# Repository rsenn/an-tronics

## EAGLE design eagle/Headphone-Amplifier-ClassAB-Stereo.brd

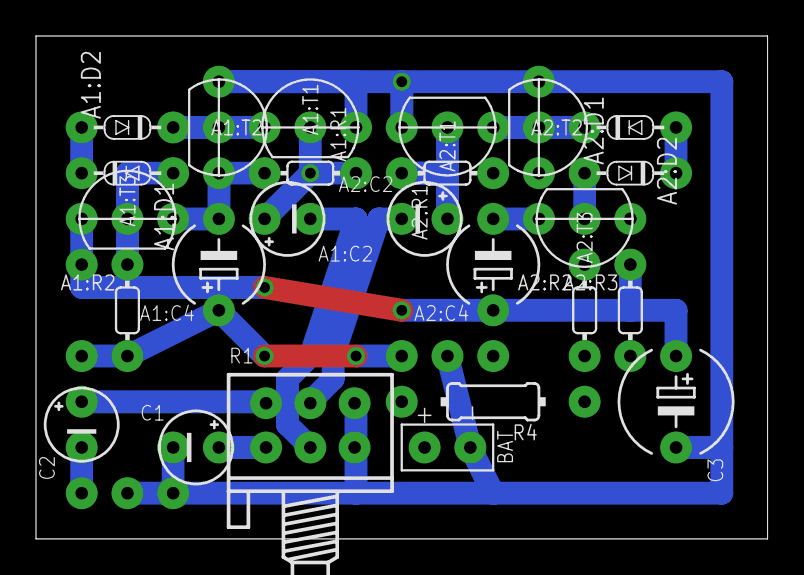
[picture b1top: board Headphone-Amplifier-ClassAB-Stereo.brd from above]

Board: 2 copper layers, 40.6 x 27.9 mm, 28 parts (1 on the bottom side), 21 nets.

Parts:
A1:C2, A2:C2: 4.7μF; E2,5-4
A1:C4, A2:C4: 220μF; E5-5/V
A1:D1, A1:D2, A2:D1, A2:D2: 1N4148; DO34-5V
A1:R1, A2:R1: 100kΩ; 0202/5-V
A1:R2, A2:R2: 330; 0202/5-V
A1:R3, A2:R3: 100; 0202/5-V
A1:T1, A1:T3, A2:T1, A2:T3: BC547; TO92-CBE
A1:T2, A2:T2: BC557; TO92-CBE
BAT: SPAD+-+-; SPAD+-
C1, C2: 4.7μF; E2,5-4
C3: 100-1000μF; E5-6
IN: SAUDIO; SPAD-3
OUT: SAUDIO; SPAD-3
R1: POT-STEREO; POT-STEREO-2X3
R4: 22Ω; 0204/10

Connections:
+3V: BAT.2, R4.2
A1:N$1: A1:D1.A, A1:R2.1, A1:T3.B
A1:N$2: A1:D2.C, A1:T1.C, A1:T2.B
A1:N$3: A1:D1.C, A1:D2.A
A1:N$4: A1:C4.-, A1:R1.2, A1:T2.E, A1:T3.E
A1:N$7: A1:C2.+, A1:R1.1, A1:T1.B
A2:N$1: A2:D1.A, A2:R2.1, A2:T3.B
A2:N$2: A2:D2.C, A2:T1.C, A2:T2.B
A2:N$3: A2:D1.C, A2:D2.A
A2:N$4: A2:C4.-, A2:R1.2, A2:T2.E, A2:T3.E
A2:N$7: A2:C2.+, A2:R1.1, A2:T1.B
GND: A1:T1.E, A1:T2.C, A2:T1.E, A2:T2.C, BAT.1, C3.-, IN.2, OUT.2, R1.1-E, R1.2-E
unnamed: A1:R3.1, A1:T3.C, A2:R3.1, A2:T3.C, C3.+, R4.1
unnamed: A1:C4.+, A1:R2.2, A1:R3.2, OUT.1
unnamed: C2.-, IN.3
unnamed: C2.+, R1.2-A
unnamed: C1.+, R1.1-A
unnamed: A1:C2.-, R1.1-S
unnamed: A2:C2.-, R1.2-S
unnamed: A2:C4.+, A2:R2.2, A2:R3.2, OUT.3
unnamed: C1.-, IN.1

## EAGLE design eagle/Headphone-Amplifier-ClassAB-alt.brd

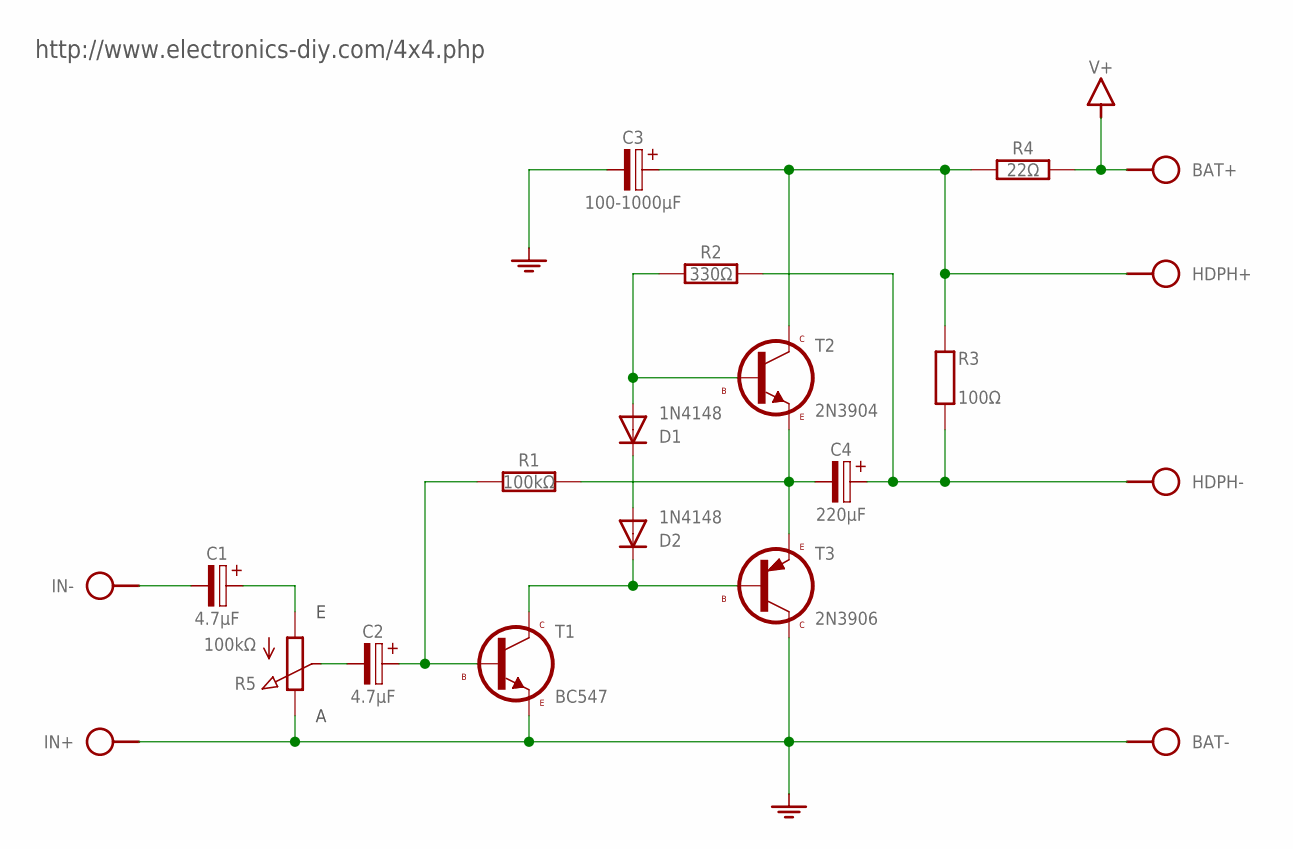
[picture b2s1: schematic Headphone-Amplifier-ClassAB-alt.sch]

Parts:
BAT: SPAD+-+-; SPAD+-
C1, C2: 4.7μF; E2,5-3
C3: 100-1000μF; E2.5-4/V
C4: 220μF; E5-4
D1: 1N4148; DO34-5-V
D2: 1N4148; DO34-5V
HDPH: SPAD+--+; SPAD-+
IN: SPAD+-+-; SPAD+-
R1: 100kΩ; 0204/10
R2: 330Ω; 0204/10
R3: 100Ω; 0204/10
R4: 22Ω; 0204/10
R5: 100kΩ; CONN-3P
T1: BC547; TO92
T2: 2N3904; TO92
T3: 2N3906; TO92

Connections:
GND: BAT.1, C3.-, IN.2, R5.3 (E), T1.1 (E), T3.3 (C)
unnamed: D1.A, R2.1, T2.2 (B)
unnamed: D2.C, T1.3 (C), T3.2 (B)
unnamed: D1.C, D2.A
unnamed: C1.+, R5.1 (A)
unnamed: C2.-, R5.2 (S)
unnamed: C2.+, R1.1, T1.2 (B)
unnamed: C3.+, HDPH.2, R3.1 (2), R4.1, T2.3 (C)
unnamed: C4.+, HDPH.1, R2.2, R3.2 (1)
unnamed: C1.-, IN.1
T3: C4.-, R1.2, T2.1 (E), T3.1 (E)
V+: BAT.2, R4.2

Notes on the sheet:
http://www.electronics-diy.com/4x4.php

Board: 2 copper layers, 17 parts (0 on the bottom side), 12 nets, no tracks yet.

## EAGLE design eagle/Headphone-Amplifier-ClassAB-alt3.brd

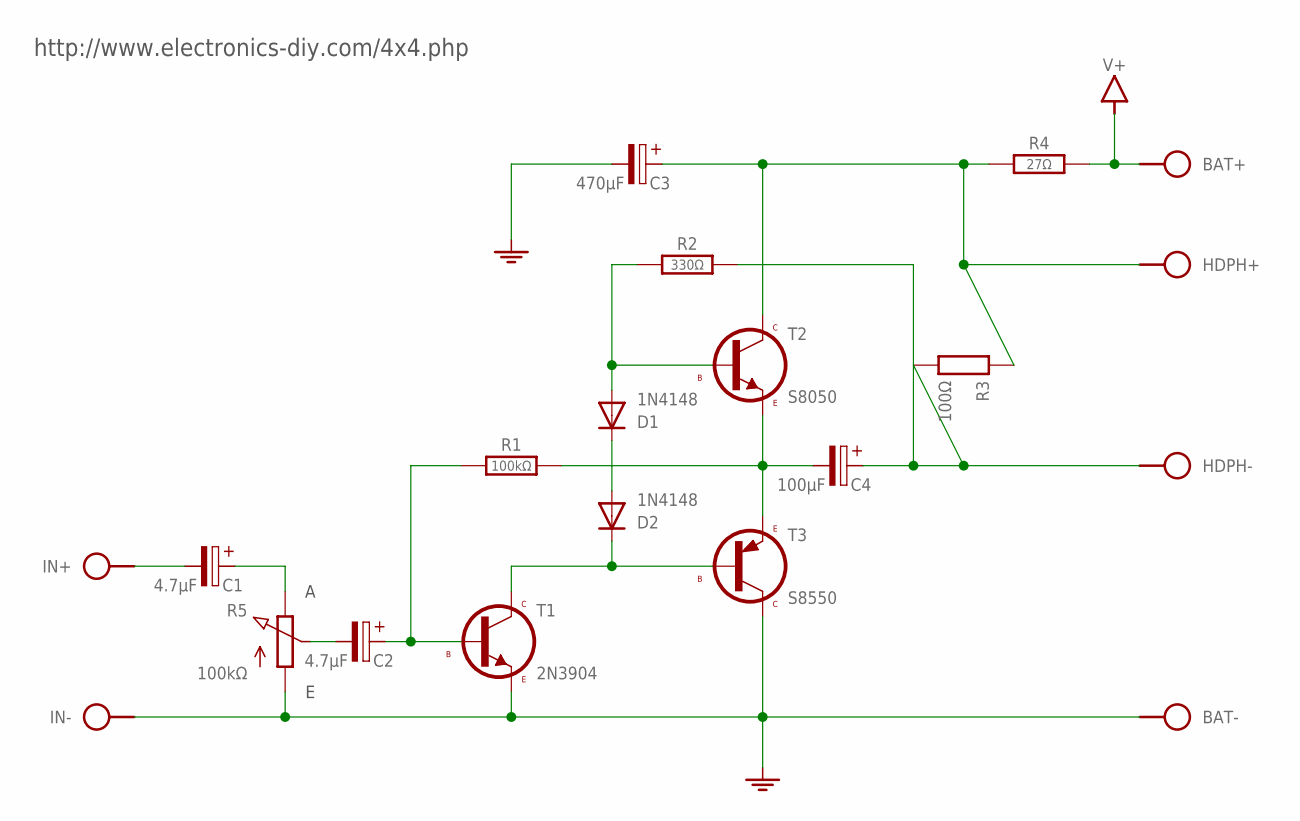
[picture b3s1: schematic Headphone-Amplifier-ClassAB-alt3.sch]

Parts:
BAT: SPAD+-+-; SPAD+-
C1, C2: 4.7μF; E2,5-3
C3: 470μF; E2,5-5/V
C4: 100μF; E5-4
D1: 1N4148; DO34-5-V
D2: 1N4148; DO34-5V
HDPH: SPAD+--+; SPAD-+
IN: SPAD+--+; SPAD-+
R1: 100kΩ; 0204/10
R2: 330Ω; 0204/10
R3: 100Ω; 0204/10
R4: 27Ω; 0204/10
R5: 100kΩ; CONN-3P
T1: 2N3904; TO92-EBC
T2: S8050; TO92-EBC
T3: S8550; TO92-EBC

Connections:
GND: BAT.1, C3.-, IN.1, R5.1 (A), T1.E, T3.C
unnamed: D1.A, R2.1, T2.B
unnamed: D2.C, T1.C, T3.B
unnamed: D1.C, D2.A
unnamed: C4.-, R1.2, T2.E, T3.E
unnamed: C1.+, R5.3 (E)
unnamed: C2.-, R5.2 (S)
unnamed: C2.+, R1.1, T1.B
unnamed: C3.+, HDPH.2, R3.1 (2), R4.1, T2.C
unnamed: C4.+, HDPH.1, R2.2, R3.2 (1)
unnamed: C1.-, IN.2
V+: BAT.2, R4.2

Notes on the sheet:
http://www.electronics-diy.com/4x4.php

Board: 2 copper layers, 17 parts (0 on the bottom side), 12 nets, no tracks yet.

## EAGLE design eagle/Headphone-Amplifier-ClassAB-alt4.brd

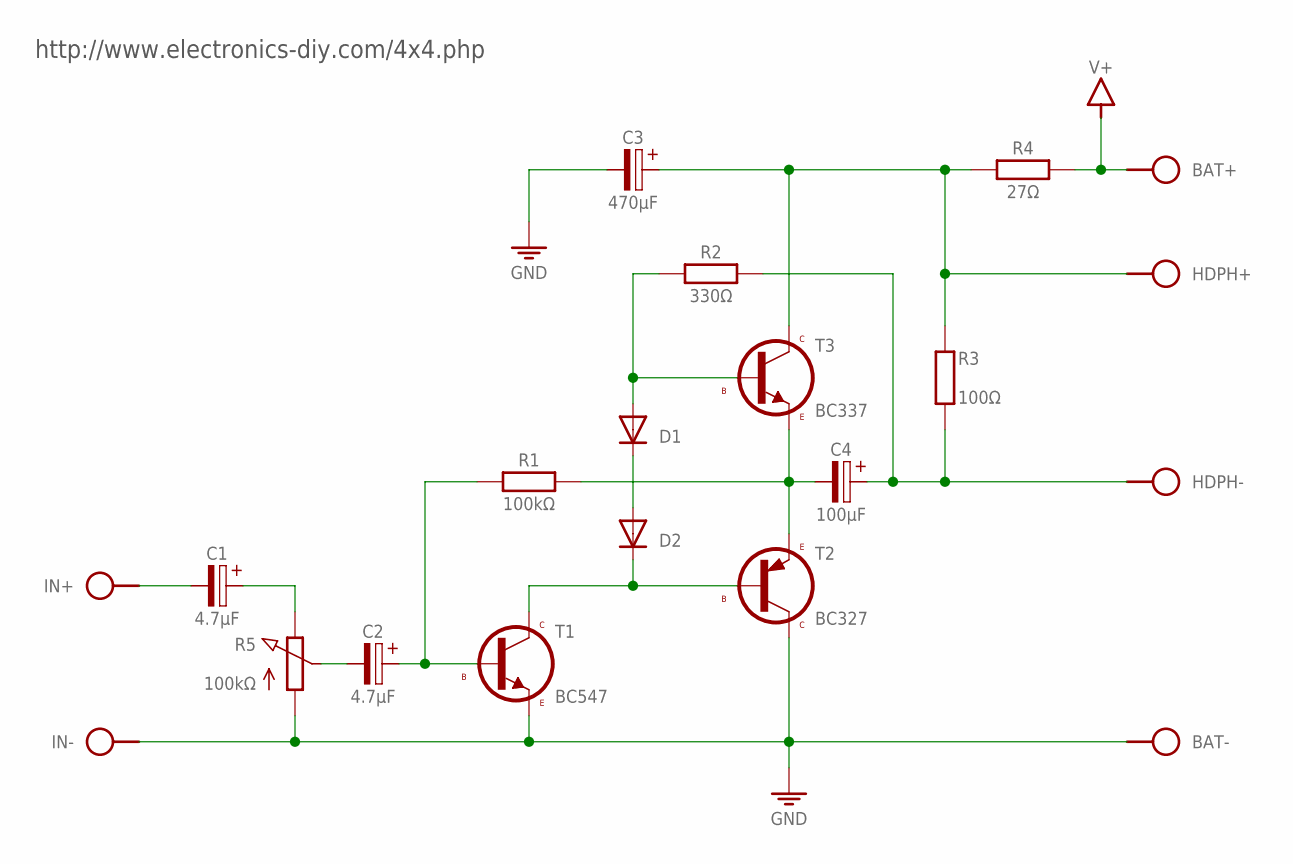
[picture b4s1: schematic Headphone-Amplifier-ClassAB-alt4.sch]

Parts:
BAT: SPAD+-+-; SPAD+-
C1, C2: 4.7μF; E2,5-4
C3: 470μF; E5-6
C4: 100μF; E5-4
D1, D2: 1N414834-5V; DO34-5V
HDPH: SPAD+--+; SPAD-+
IN: SPAD+--+; SPAD-+
R1: 100kΩ; 0202/7
R2: 330Ω; 0202/7
R3: 100Ω; 0202/7
R4: 27Ω; 0204V
R5: 100kΩ; CONN-3P
T1: BC547; TO92
T2: BC327; TO92
T3: BC337; TO92-CBE

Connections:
GND: BAT.1, C3.-, IN.1, R5.1 (A), T1.3 (E), T2.1 (C)
unnamed: D1.A, R2.1, T3.2 (B)
unnamed: D2.C, T1.1 (C), T2.2 (B)
unnamed: D1.C, D2.A
unnamed: C4.-, R1.2, T2.3 (E), T3.3 (E)
unnamed: C1.+, R5.3 (E)
unnamed: C2.-, R5.2 (S)
unnamed: C2.+, R1.1, T1.2 (B)
unnamed: C3.+, HDPH.2, R3.2 (1), R4.2 (1), T3.1 (C)
unnamed: C4.+, HDPH.1, R2.2, R3.1 (2)
unnamed: C1.-, IN.2
V+: BAT.2, R4.1 (2)

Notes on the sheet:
http://www.electronics-diy.com/4x4.php

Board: 2 copper layers, 17 parts (0 on the bottom side), 12 nets, no tracks yet.
